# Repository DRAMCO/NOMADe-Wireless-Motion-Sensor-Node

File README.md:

# NOMADe - Wireless Motion Sensor Node
 Documentation about the wireless motion sensor node.

## Software
 This map contains the c/c++ and python code for both the sensor node and receiver.
 
## Hardware
 Here you can find the Eagle schematics and STL files.

## How to cite
```LaTex
@Misc{Interreg-NOMADe,
  author =   {J. Cappelle},
  title =    {{Wireless Motion Sensor Node}},
  howpublished  = {\url{https://github.com/DRAMCO/NOMADe-Wireless-Motion-Sensor-Node}},
  doi = {10.5281/zenodo.4024373}
}
```

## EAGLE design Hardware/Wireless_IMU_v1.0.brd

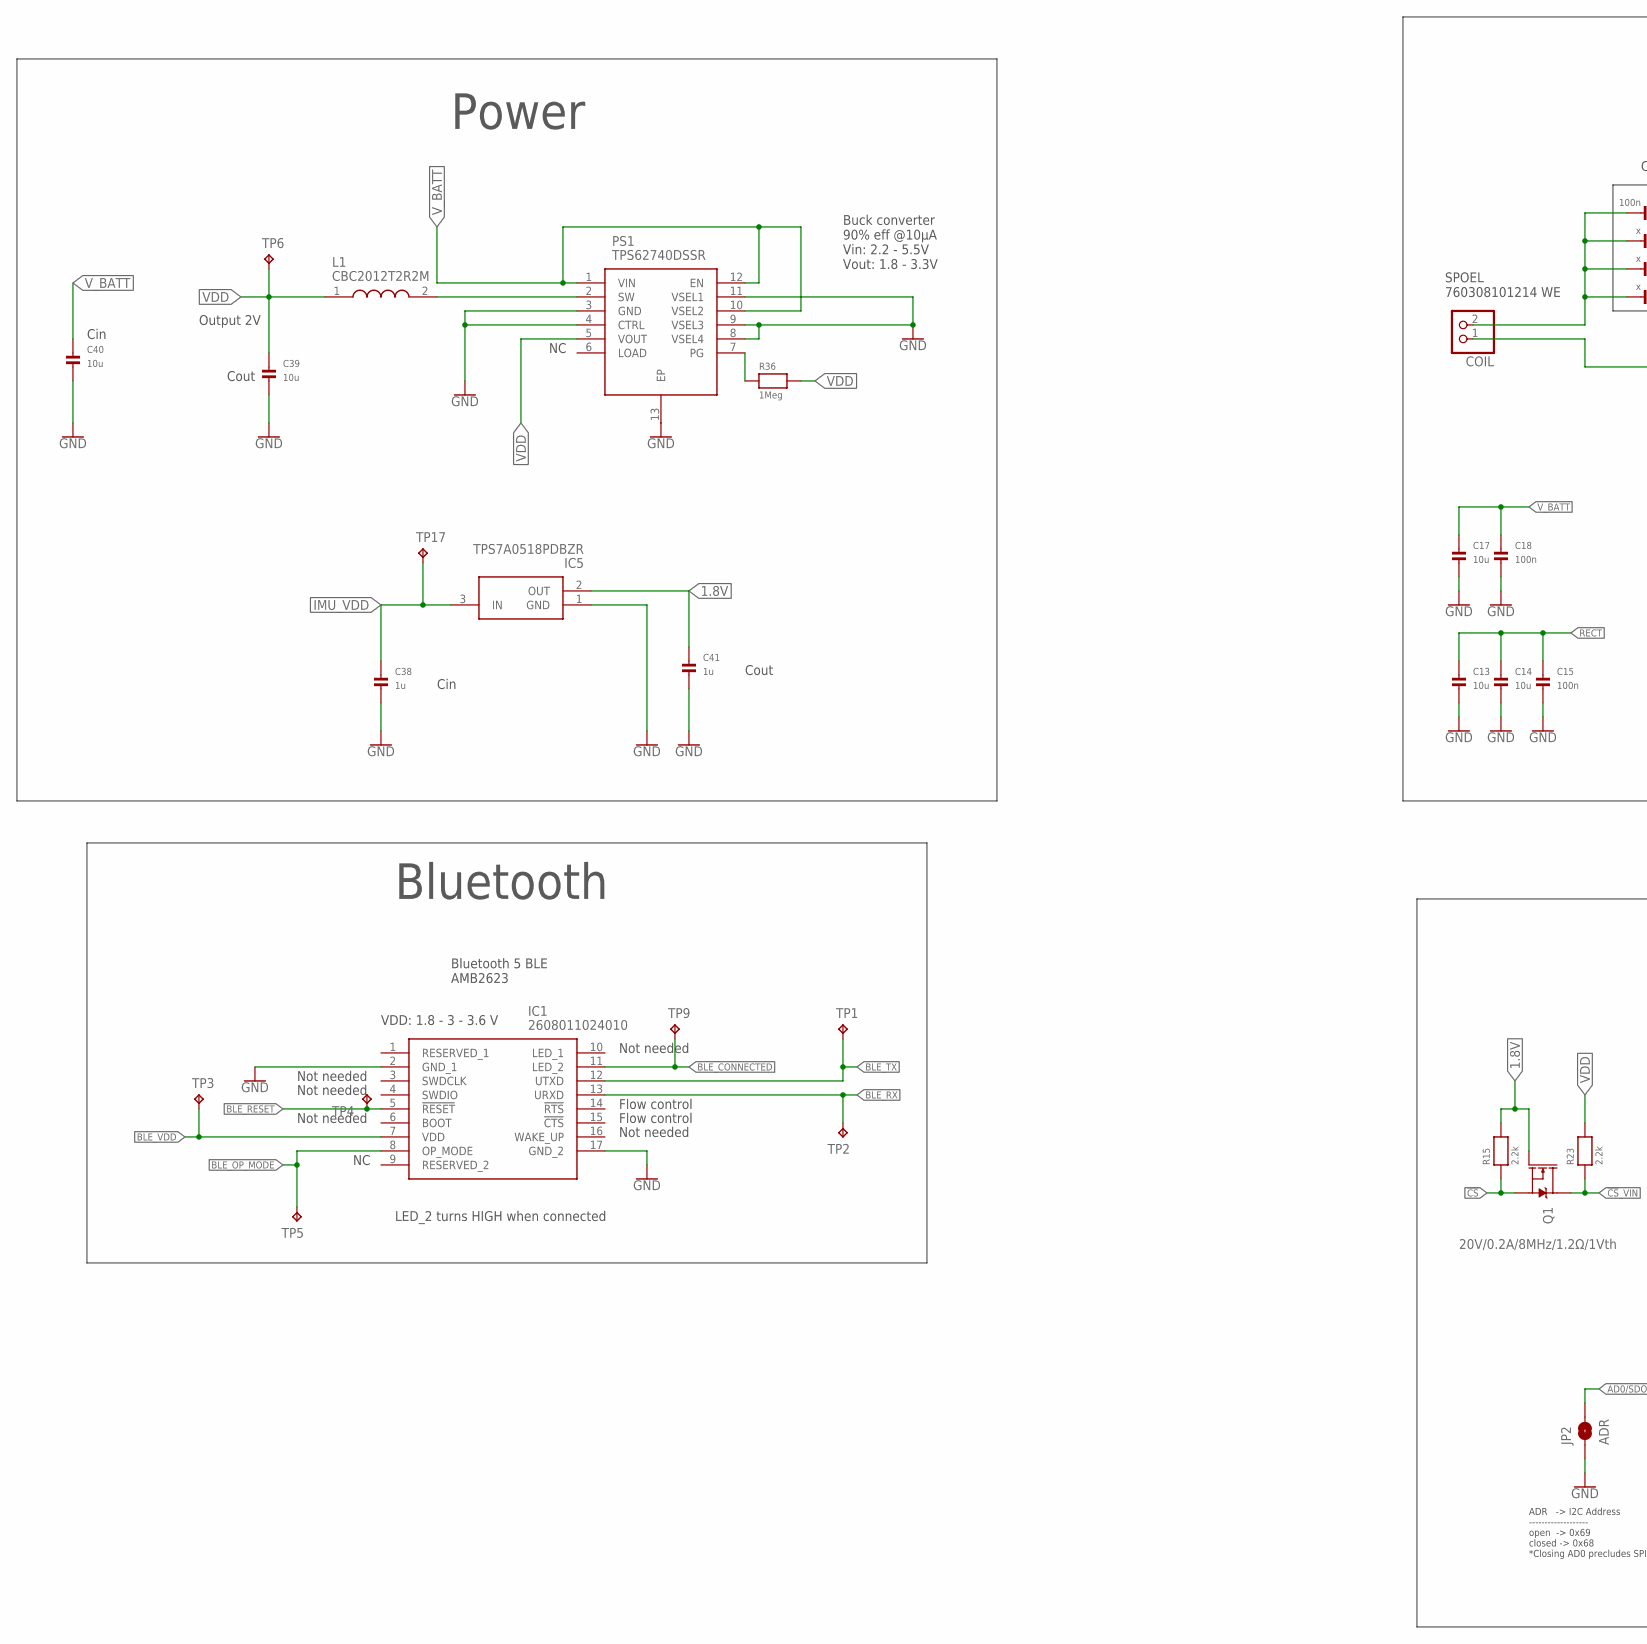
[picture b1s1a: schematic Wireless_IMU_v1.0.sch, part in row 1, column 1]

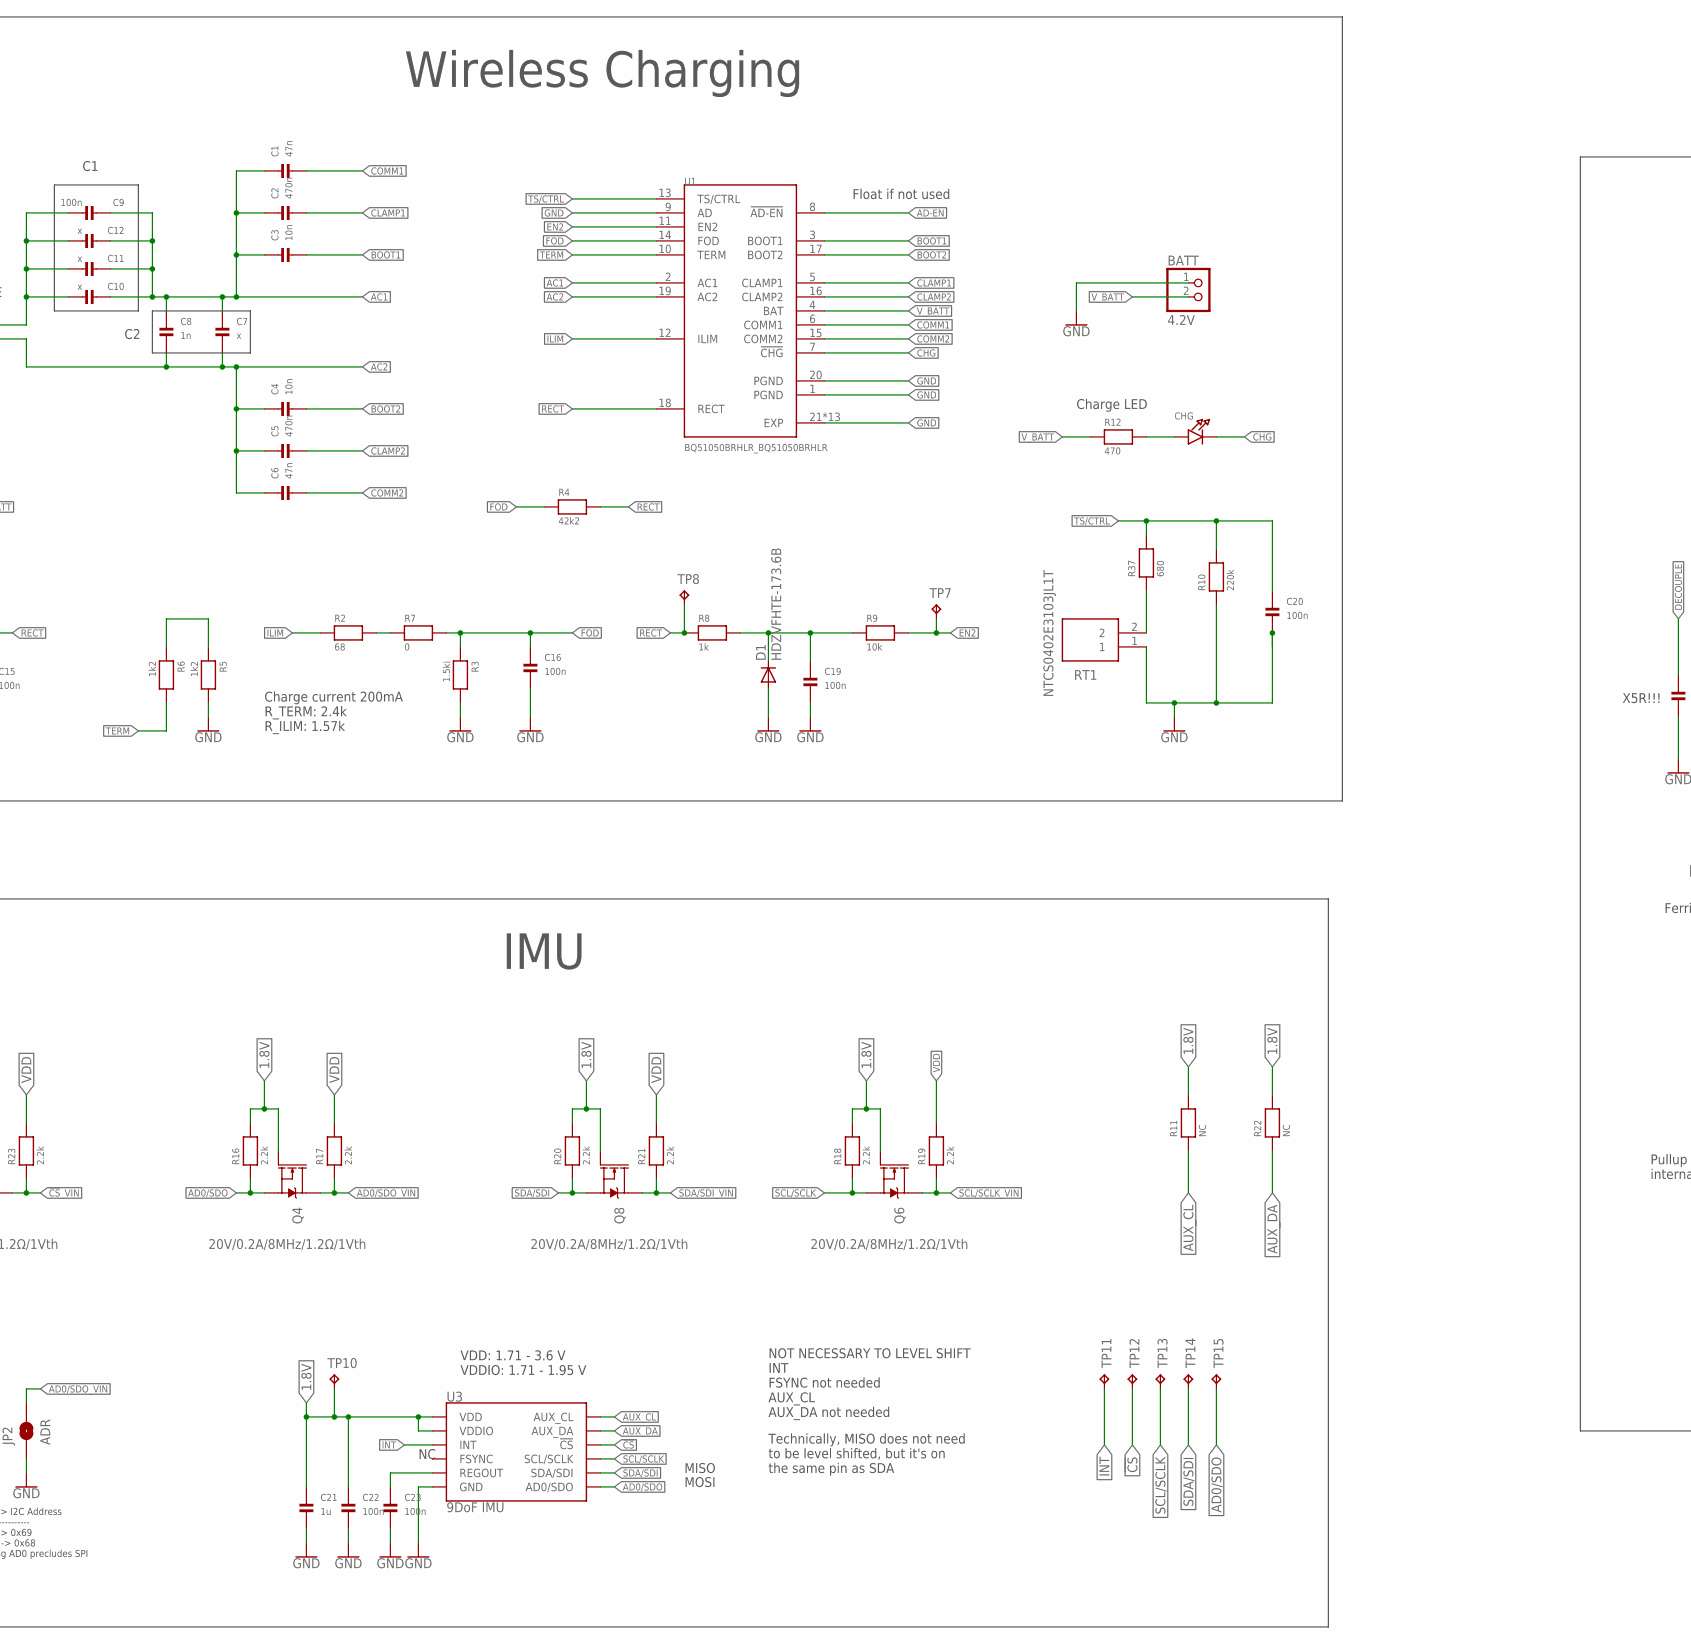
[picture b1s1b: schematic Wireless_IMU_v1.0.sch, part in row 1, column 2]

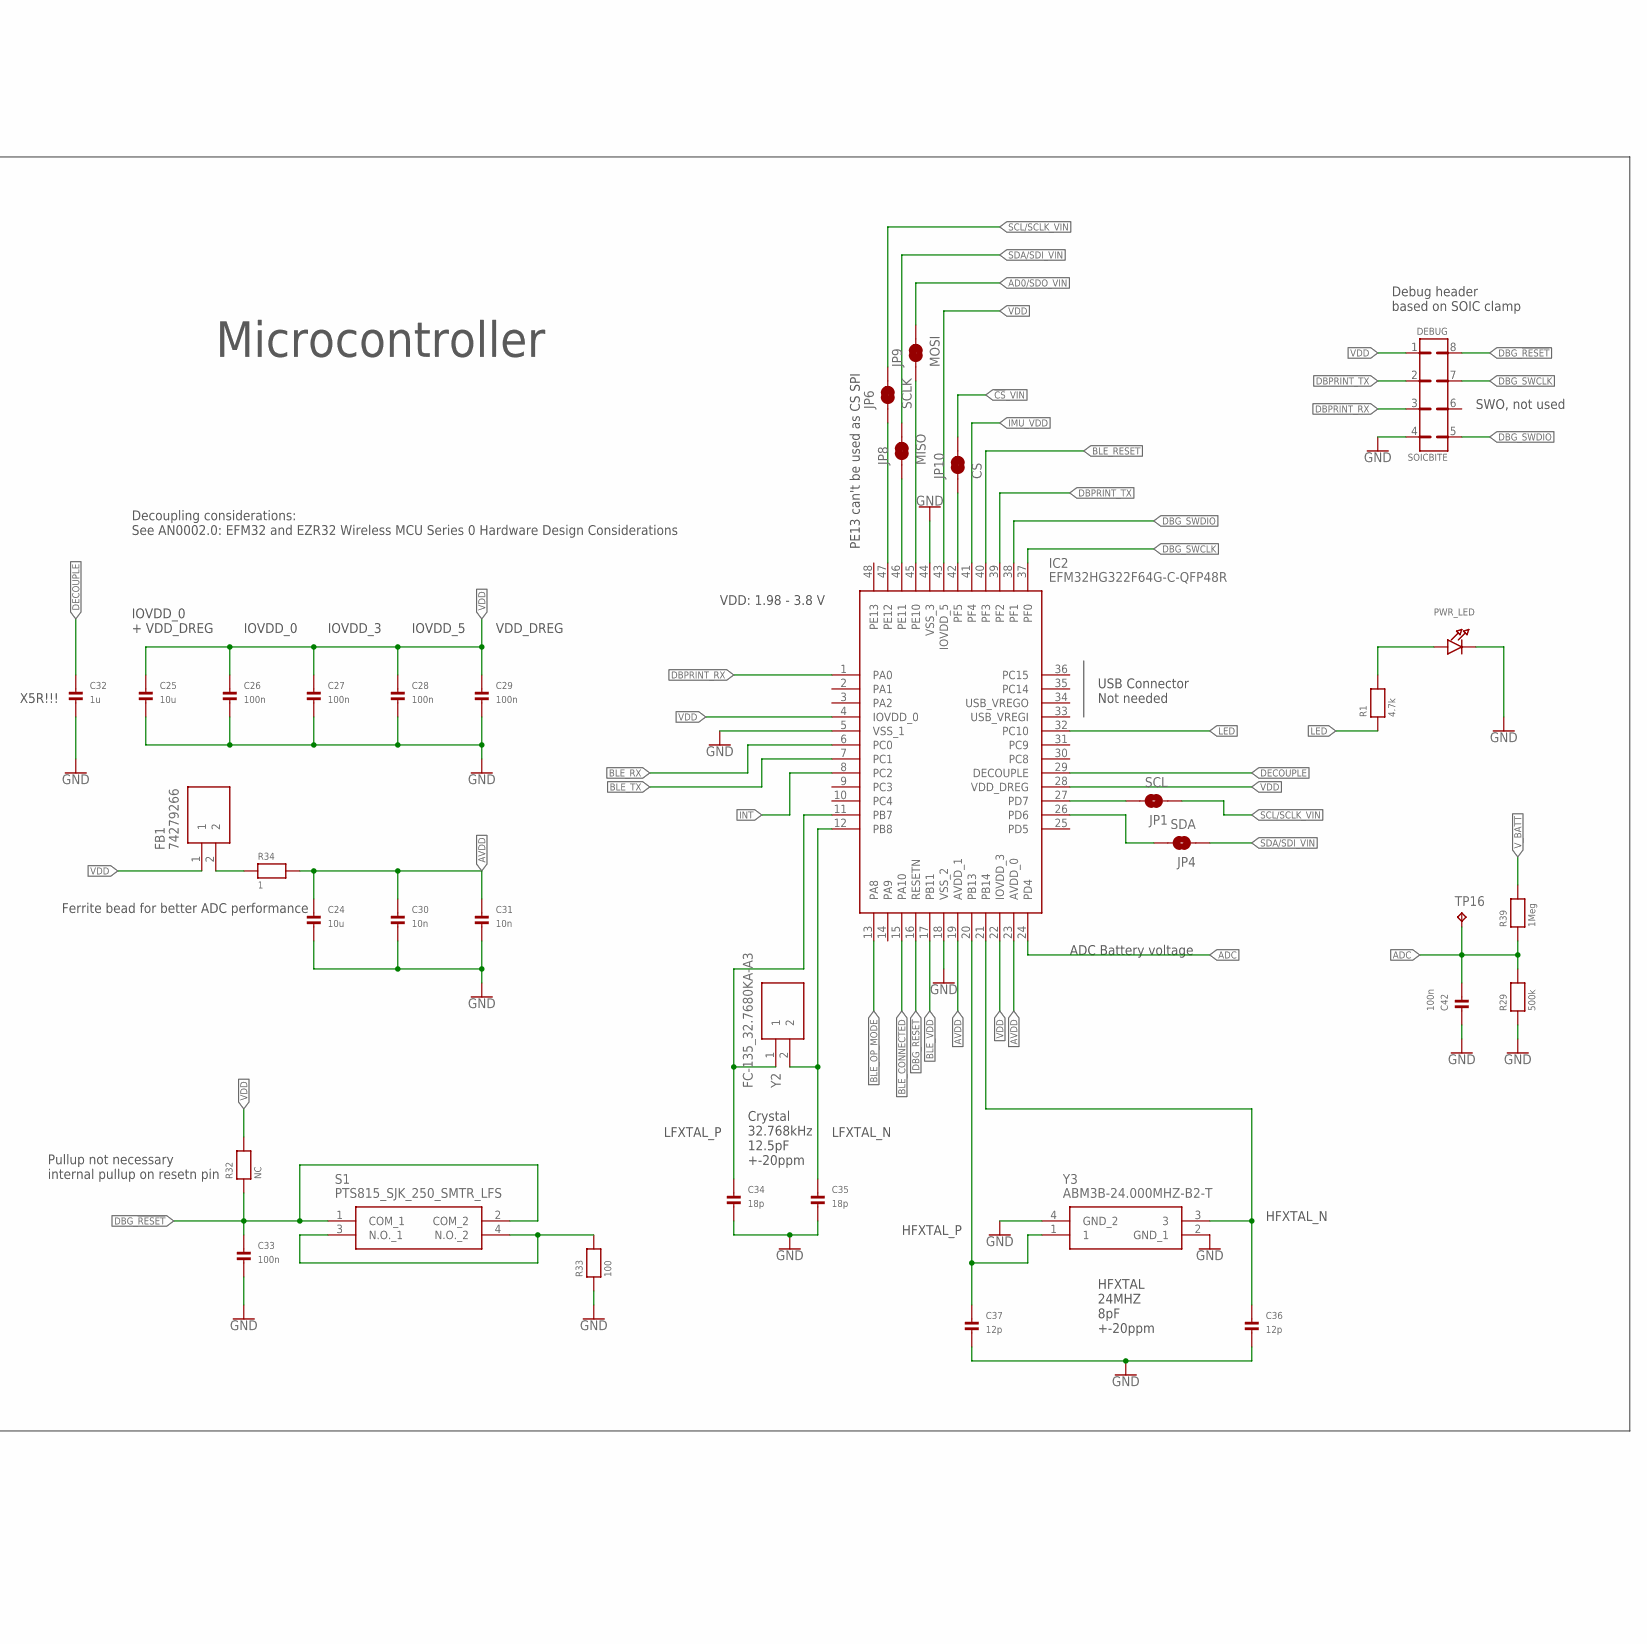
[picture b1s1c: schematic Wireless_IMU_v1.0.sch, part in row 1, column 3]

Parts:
BATT: 4.2V; 1X02
C1, C6: 47n; 0603
C2, C5: 470n; 0603
C3, C4, C30, C31: 10n; 0603
C7, C10, C11, C12: x; 0603
C8: 1n; 0603
C9, C15, C16, C18, C19, C20, C22, C23, C26, C27, C28, C29, C33, C42: 100n; 0603
C13, C14, C17, C24, C25, C39, C40: 10u; 0603
C21, C32, C38, C41: 1u; 0603
C34, C35: 18p; 0603
C36, C37: 12p; 0603
CHG: LED0805; CHIPLED_0805
COIL: PINHD-1X2; 1X02
D1: HDZVFHTE-173.6B; SOD323-W
DEBUG: SOICBITE
FB1: 74279266; BEADC1608X100N
IC1: 2608011024010
IC2: EFM32HG322F64G-C-QFP48R; QFP50P900X900X120-48N
IC5: TPS7A0518PDBZR; SOT95P237X112-3N
JP1: SCL; SMT-JUMPER_2_NO_SILK
JP2: ADR; SMT-JUMPER_2_NO_SILK
JP4: SDA; SMT-JUMPER_2_NO_SILK
JP6: SCLK; SMT-JUMPER_2_NC_TRACE_SILK
JP8: MISO; SMT-JUMPER_2_NC_TRACE_SILK
JP9: MOSI; SMT-JUMPER_2_NC_TRACE_SILK
JP10: CS; SMT-JUMPER_2_NC_TRACE_SILK
L1: CBC2012T2R2M; INDC2012X145N
PS1: TPS62740DSSR; SON50P200X300X80-13N
PWR_LED: LED0805; CHIPLED_0805
Q1, Q4, Q6, Q8: 20V/0.2A/8MHz/1.2Ω/1Vth; SOT-416FL
R1: 4.7k; 0603
R2: 68; 0603
R3: 1.5ki; 0603
R4: 42k2; 0603
R5, R6: 1k2; 0603
R7: 0; 0603
R8: 1k; 0603
R9: 10k; 0603
R10: 220k; 0603
R11, R22, R32: NC; 0603
R12: 470; 0603
R15, R16, R17, R18, R19, R20, R21, R23: 2.2k; 0603
R29: 500k; 0603
R33: 100; 0603
R34: 1; 0603
R36, R39: 1Meg; 0603
R37: 680; 0603
RT1: NTCS0402E3103JL1T; CAPC1005X65N
S1: PTS815_SJK_250_SMTR_LFS; PTS815SJK250SMTRLFS
TP1, TP2, TP3, TP4, TP5, TP6, TP7, TP8, TP9, TP10, TP11, TP12, TP13, TP14, TP15, TP16, TP17: TPTP10R; TP10R
U1: BQ51050BRHLR_BQ51050BRHLR; BQ51050BRHLR_QFN50P450X350X100-21N
U3: 9DoF IMU; SPARKFUN-SENSORS_QFN24-3X3
Y2: FC-135_32.7680KA-A3; FC135327680KAAG0
Y3: ABM3B-24.000MHZ-B2-T; ABM3B8000MHZ101UT

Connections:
1.8V: C21.1, C22.1, C41.1, IC5.2 (OUT), Q1.1 (G), Q4.1 (G), Q6.1 (G), Q8.1 (G), R11.2, R15.2, R16.2, R18.2, R20.2, R22.2, TP10.TP, U3.8 (VDDIO), U3.13 (VDD)
!CS: Q1.2 (S), R15.1, TP12.TP, U3.22 (!CS)
!CS!_VIN: JP10.2, Q1.3 (D), R23.1
AC1: C1.1, C2.1, C3.1, C7.1, C8.1, C9.2, C10.2, C11.2, C12.2, U1.2 (AC1)
AC2: C4.1, C5.1, C6.1, C7.2, C8.2, COIL.1, U1.19 (AC2)
AC11: C9.1, C10.1, C11.1, C12.1, COIL.2
AD0/SDO: Q4.2 (S), R16.1, TP15.TP, U3.9 (AD0/SDO)
AD0/SDO_VIN: JP2.2, JP9.2, Q4.3 (D), R17.1
AD-EN: U1.8 (!AD-EN)
ADC: C42.1, IC2.24 (PD4), R29.2, R39.1, TP16.TP
AUX_CL: R11.1, U3.7 (AUX_CL)
AUX_DA: R22.1, U3.21 (AUX_DA)
AVDD: C24.1, C30.1, C31.1, IC2.19 (AVDD_1), IC2.23 (AVDD_0), R34.2
BLE_CONNECTED: IC1.11 (LED_2), IC2.15 (PA10), TP9.TP
BLE_OP_MODE: IC1.8 (OP_MODE), IC2.13 (PA8), TP5.TP
BLE_RESET: IC1.5 (!RESET), IC2.40 (PF3), TP4.TP
BLE_RX: IC1.13 (URXD), IC2.6 (PC0), TP2.TP
BLE_TX: IC1.12 (UTXD), IC2.7 (PC1), TP1.TP
BLE_VDD: IC1.7 (VDD), IC2.17 (PB11), TP3.TP
BOOT1: C3.2, U1.3 (BOOT1)
BOOT2: C4.2, U1.17 (BOOT2)
CHG: CHG.C, U1.7 (!CHG)
CLAMP1: C2.2, U1.5 (CLAMP1)
CLAMP2: C5.2, U1.16 (CLAMP2)
COMM1: C1.2, U1.6 (COMM1)
COMM2: C6.2, U1.15 (COMM2)
DBG_!RESET: C33.1, DEBUG.8, IC2.16 (RESETN), R32.1, S1.1 (COM_1), S1.2 (COM_2)
DBG_SWCLK: DEBUG.7, IC2.37 (PF0)
DBG_SWDIO: DEBUG.5, IC2.38 (PF1)
DBPRINT_RX: DEBUG.3, IC2.1 (PA0)
DBPRINT_TX: DEBUG.2, IC2.39 (PF2)
DECOUPLE: C32.1, IC2.29 (DECOUPLE)
EN2: R9.2, TP7.TP, U1.11 (EN2)
FOD: C16.1, R3.1, R4.1, R7.2, U1.14 (FOD)
GND: BATT.1, C13.2, C14.2, C15.2, C16.2, C17.2, C18.2, C19.2, C20.2, C21.2, C22.2, C23.2, C24.2, C25.2, C26.2, C27.2, C28.2, C29.2, C30.2, C31.2, C32.2, C33.2, C34.2, C35.2, C36.2, C37.2, C38.2, C39.2, C40.2, C41.2, C42.2, D1.A, DEBUG.4, IC1.2 (GND_1), IC1.17 (GND_2), IC2.5 (VSS_1), IC2.18 (VSS_2), IC2.44 (VSS_3), IC5.1 (GND), JP2.1, PS1.3 (GND), PS1.4 (CTRL), PS1.8 (VSEL4), PS1.9 (VSEL3), PS1.11 (VSEL1), PS1.13 (EP), PWR_LED.C, R3.2, R5.2, R10.1, R29.1, R33.1, RT1.1, U1.1 (PGND), U1.9 (AD), U1.20 (PGND), U1.21 (EXP), U1.22 (EXP), U1.23 (EXP), U1.24 (EXP), U1.25 (EXP), U1.26 (EXP), U1.27 (EXP), U1.28 (EXP), U1.29 (EXP), U1.30 (EXP), U1.31 (EXP), U1.32 (EXP), U1.33 (EXP), U3.18 (GND), U3.20 (GND), Y3.2 (GND_1), Y3.4 (GND_2)
ILIM: R2.1, U1.12 (ILIM)
IMU_VDD: C38.1, IC2.41 (PF4), IC5.3 (IN), TP17.TP
INT: IC2.8 (PC2), TP11.TP, U3.12 (INT)
LED: IC2.32 (PC10), R1.1
unnamed: IC2.27 (PD7), JP1.2
unnamed: R5.1, R6.1
unnamed: PWR_LED.A, R1.2
unnamed: R2.2, R7.1
unnamed: CHG.A, R12.2
unnamed: C19.1, D1.C, R8.2, R9.1
unnamed: IC2.26 (PD6), JP4.2
unnamed: IC2.47 (PE12), JP6.1
unnamed: C35.1, IC2.12 (PB8), Y2.2
unnamed: C23.1, U3.10 (REGOUT)
unnamed: IC2.46 (PE11), JP8.1
unnamed: IC2.45 (PE10), JP9.1
unnamed: C34.1, IC2.11 (PB7), Y2.1
unnamed: IC2.42 (PF5), JP10.1
unnamed: C37.1, IC2.20 (PB13), Y3.1
unnamed: C36.1, IC2.21 (PB14), Y3.3
unnamed: R33.2, S1.3 (N.O._1), S1.4 (N.O._2)
unnamed: FB1.2, R34.1
unnamed: R37.1, RT1.2
unnamed: L1.2, PS1.2 (SW)
unnamed: PS1.7 (PG), R36.1
RECT: C13.1, C14.1, C15.1, R4.2, R8.1, TP8.TP, U1.18 (RECT)
SCL/SCLK: Q6.2 (S), R18.1, TP13.TP, U3.23 (SCL/SCLK)
SCL/SCLK_VIN: JP1.1, JP6.2, Q6.3 (D), R19.1
SDA/SDI: Q8.2 (S), R20.1, TP14.TP, U3.24 (SDA/SDI)
SDA/SDI_VIN: JP4.1, JP8.2, Q8.3 (D), R21.1
TERM: R6.2, U1.10 (TERM)
TS/CTRL: C20.1, R10.2, R37.2, U1.13 (TS/CTRL)
VDD: C25.1, C26.1, C27.1, C28.1, C29.1, C39.1, DEBUG.1, FB1.1, IC2.4 (IOVDD_0), IC2.22 (IOVDD_3), IC2.28 (VDD_DREG), IC2.43 (IOVDD_5), L1.1, PS1.5 (VOUT), R17.2, R19.2, R21.2, R23.2, R32.2, R36.2, TP6.TP
V_BATT: BATT.2, C17.1, C18.1, C40.1, PS1.1 (VIN), PS1.10 (VSEL2), PS1.12 (EN), R12.1, R39.2, U1.4 (BAT)

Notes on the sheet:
Wireless Charging
Bluetooth
IMU
Microcontroller
VDD: 1.8 - 3 - 3.6 V
Bluetooth 5 BLE AMB2623
ADR -> I2C Address ------------------- open -> 0x69 closed -> 0x68 *Closing AD0 precludes SPI
SPOEL 760308101214 WE
VDD: 1.71 - 3.6 V VDDIO: 1.71 - 1.95 V
Not needed
Flow control
USB Connector Not needed
X5R!!!
Crystal 32.768kHz 12.5pF +-20ppm
HFXTAL 24MHZ 8pF +-20ppm
HFXTAL_P
HFXTAL_N
LFXTAL_P
LFXTAL_N
Ferrite bead for better ADC performance
IOVDD_0 + VDD_DREG
IOVDD_0
IOVDD_3
IOVDD_5
Decoupling considerations: See AN0002.0: EFM32 and EZR32 Wireless MCU Series 0 Hardware Design Considerations
Pullup not necessary internal pullup on resetn pin
Debug header based on SOIC clamp
Power
VDD: 1.98 - 3.8 V
Buck converter 90% eff @10µA Vin: 2.2 - 5.5V Vout: 1.8 - 3.3V
Output 2V
Cout
Cin
PE13 can't be used as CS SPI
NOT NECESSARY TO LEVEL SHIFT INT FSYNC not needed AUX_CL AUX_DA not needed
MISO
MOSI
Technically, MISO does not need to be level shifted, but it's on the same pin as SDA
ADC Battery voltage
VDD_DREG

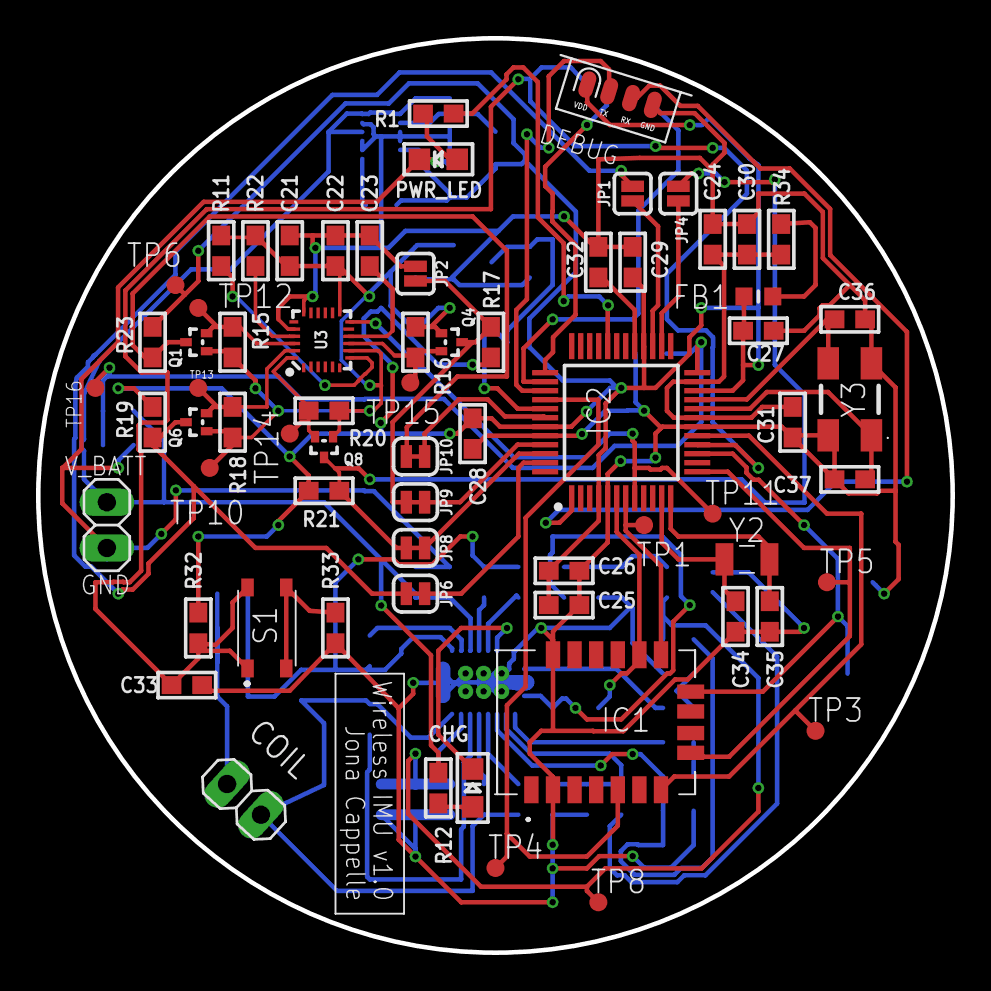
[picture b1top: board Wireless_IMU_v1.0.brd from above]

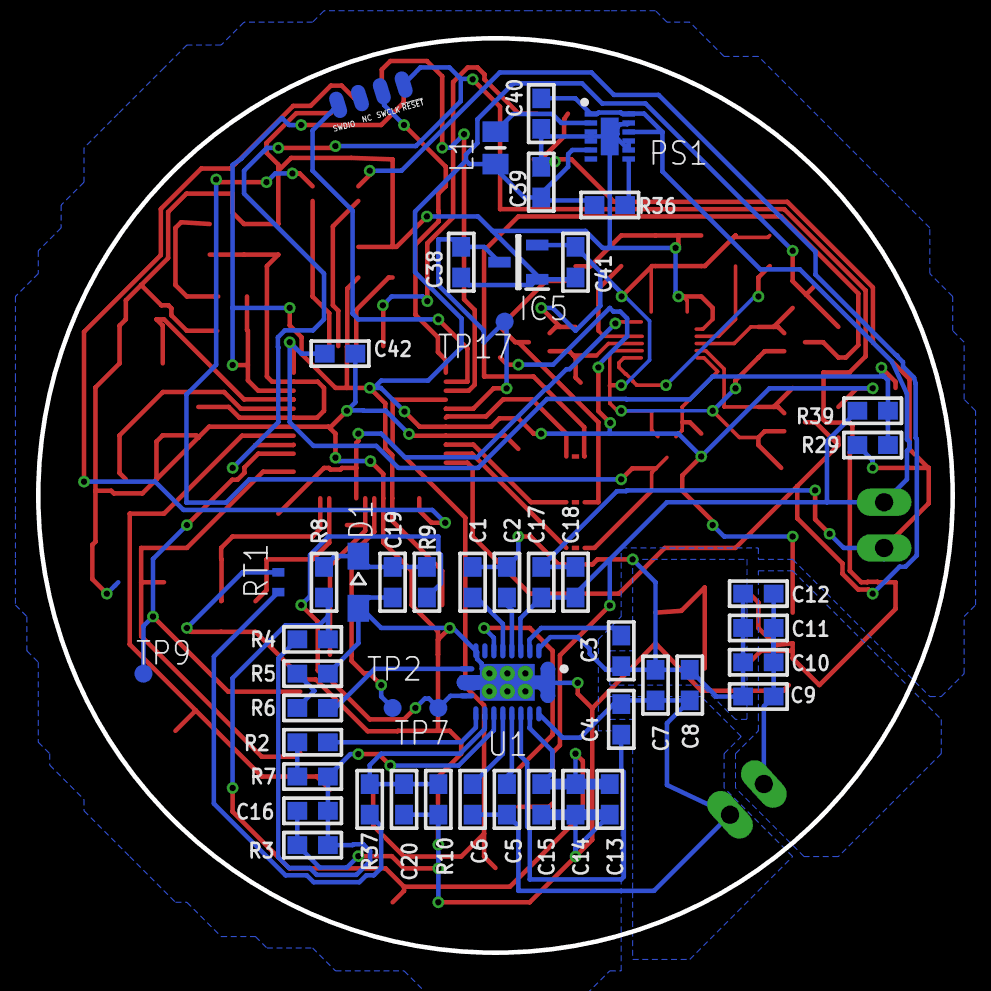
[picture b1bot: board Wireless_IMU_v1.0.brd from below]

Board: 2 copper layers, 50.8 x 50.8 mm, 116 parts (48 on the bottom side), 68 nets.

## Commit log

2020-09-11 v1.0
2020-09-11 cleanup
2020-09-11 STL files

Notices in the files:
parts and their libraries:
microbuilder: This work is placed in the public domain, and may be freely used for commercial and non-commercial work with the following conditions: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
SparkFun-Jumpers: Licensing: Creative Commons ShareAlike 4.0 International - https://creativecommons.org/licenses/by-sa/4.0
